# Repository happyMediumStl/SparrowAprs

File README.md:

# SparrowAprs
An open source APRS beacon designed for high altitude balloons

Code is a bit of a mess, and this is a work in progress, but it does sucessfully transmit APRS packets

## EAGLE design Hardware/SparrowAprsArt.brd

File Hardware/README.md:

#SparrowAprs Hardware

Controlled impedance traces designed for 4 layer stackup at Oshpark.

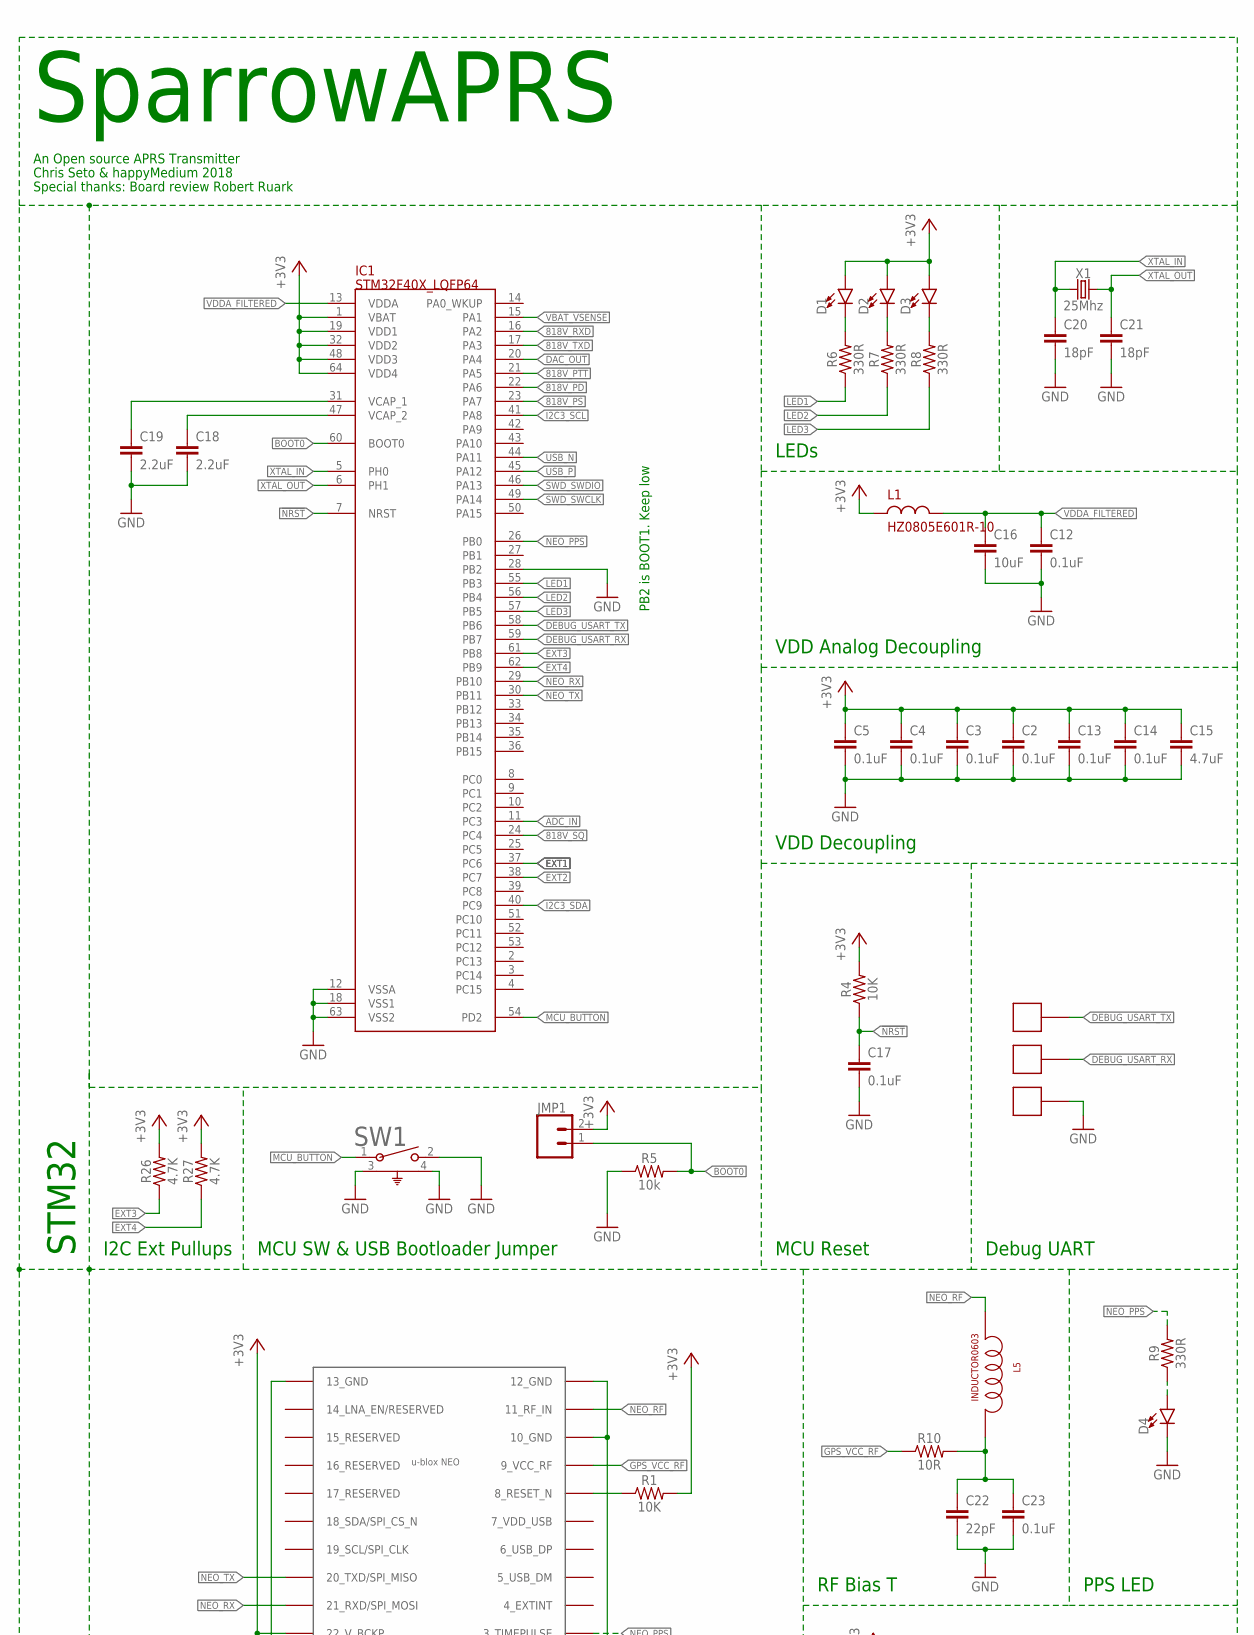
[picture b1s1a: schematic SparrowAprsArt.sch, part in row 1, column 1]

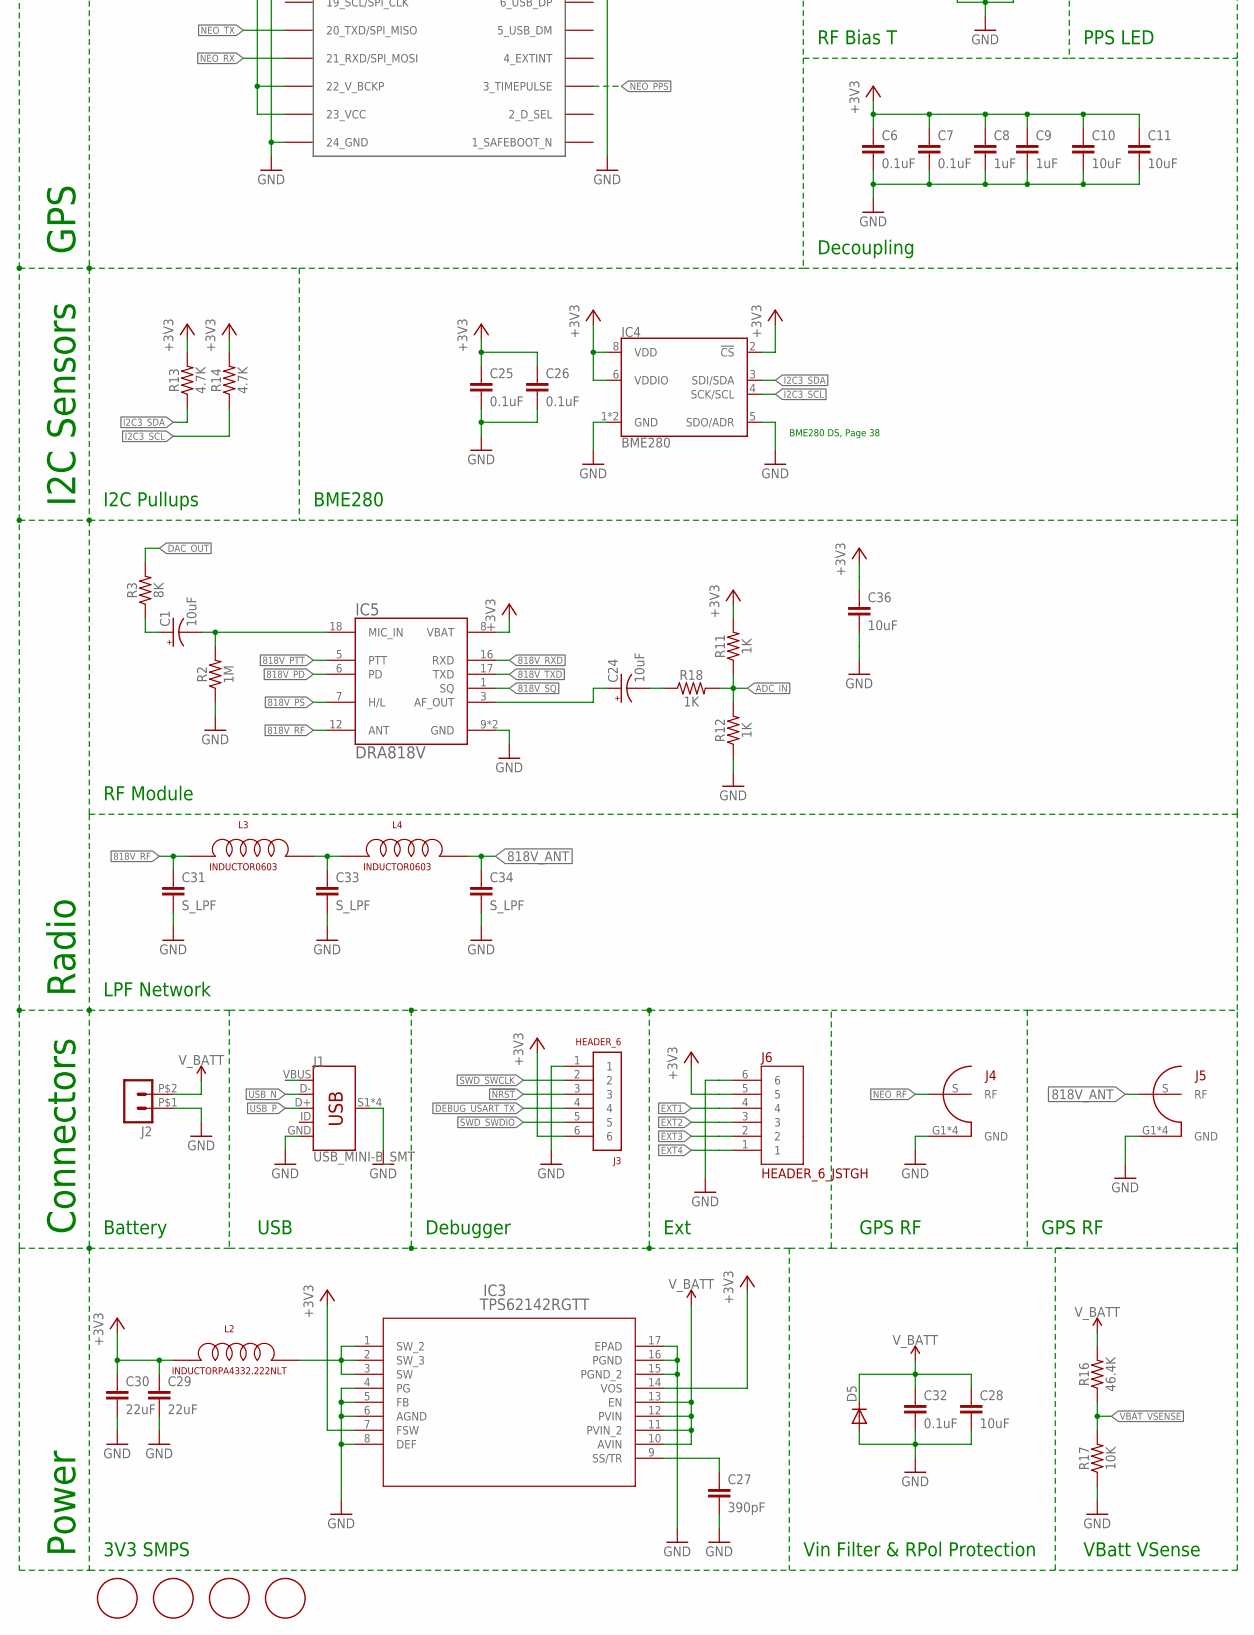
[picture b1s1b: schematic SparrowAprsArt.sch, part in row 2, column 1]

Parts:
C1, C24: 10uF; 1206
C2, C3, C4, C5, C6, C7, C12, C13, C14, C17, C23, C25, C26, C32: 0.1uF; 0603
C8, C9: 1uF; C0805
C10, C11, C16, C28, C36: 10uF; C0805
C15: 4.7uF; C0805
C18, C19: 2.2uF; C0805
C20, C21: 18pF; 0603
C22: 22pF; 0603
C27: 390pF; 0603
C29, C30: 22uF; 1210
C31, C33, C34: S_LPF; 0603
D1, D2, D3, D4: LED0603; LED-0603
D5: DIODE-DO214AC; DO214AC
IC1: STM32F40X_LQFP64; STM32_LQFP64
IC2: NEO-M8
IC3: TPS62142RGTT; RGT16_1P7X1P7
IC4: BME280; LGA-8-2.5X2.5
IC5: DRA818V; DORJI_DRA818V
J1: USB_MINI-B_SMT; USB-MINIB
J2: HEADER_POS2_43650-0200; 43650-0200
J3: HEADER_6; 6X2_SMT
J4, J5: FSK_RUARK2_SMA_0732511150; FSK_RUARK2_WIDE_SMA
J6: HEADER_6_JSTGH; BM06B-GHS-TBT(LF)(SN)(N)
JMP1: CONN_02; 1X02
L1: HZ0805E601R-10; R0805
L2: INDUCTORPA4332.222NLT; PA4332.222NLT
L3, L4, L5: INDUCTOR0603; 0603
R1, R4, R17: 10K; 0603
R2: 1M; 0603
R3: 8K; 0603
R5: 10k; 0603
R6, R7, R8, R9: 330R; 0603
R10: 10R; 0603
R11, R12, R18: 1K; 0603
R13, R14, R26, R27: 4.7K; 0603
R16: 46.4K; 0603
SW1: 1825027-8; SW2_1825027-C
U$2, U$3, U$4: SINGLEPADMIDPAD; MIDPAD
U$7, U$8, U$9, U$10: MOUNTING_HOLE#2; #2_CLEARANCE_HOLE
X1: 25Mhz; CRYSTAL-SMD-3.2X2.5MM

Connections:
818V_ANT: C34.1, J5.S (RF), L4.2
818V_PD: IC1.22 (PA6), IC5.6 (PD)
818V_PS: IC1.23 (PA7), IC5.7 (H/L)
818V_PTT: IC1.21 (PA5), IC5.5 (PTT)
818V_RF: C31.1, IC5.12 (ANT), L3.1
818V_RXD: IC1.16 (PA2), IC5.16 (RXD)
818V_SQ: IC1.24 (PC4), IC5.1 (SQ)
818V_TXD: IC1.17 (PA3), IC5.17 (TXD)
!NRST: C17.1, IC1.7 (NRST), J3.3, R4.1
+3V3: C2.1, C3.1, C4.1, C5.1, C6.1, C7.1, C8.1, C9.1, C10.1, C11.1, C13.1, C14.1, C15.1, C25.1, C26.1, C29.1, C30.1, C36.1, D1.A, D2.A, D3.A, IC1.1 (VBAT), IC1.19 (VDD1), IC1.32 (VDD2), IC1.48 (VDD3), IC1.64 (VDD4), IC2.22 (22_V_BCKP), IC2.23 (23_VCC), IC3.7 (FSW), IC3.14 (VOS), IC4.2 (!CS), IC4.6 (VDDIO), IC4.8 (VDD), IC5.8 (VBAT), J3.6, J6.5, JMP1.2, L1.1, L2.1, R1.2, R4.2, R11.2, R13.2, R14.2, R26.2, R27.2
ADC_IN: IC1.11 (PC3), R11.1, R12.2, R18.2
BOOT0: IC1.60 (BOOT0), JMP1.1, R5.2
DAC_OUT: IC1.20 (PA4), R3.2
DEBUG_USART_RX: IC1.59 (PB7), U$3.1
DEBUG_USART_TX: IC1.58 (PB6), J3.4, U$2.1
EXT1: IC1.37 (PC6), J6.4
EXT2: IC1.38 (PC7), J6.3
EXT3: IC1.61 (PB8), J6.2, R26.1
EXT4: IC1.62 (PB9), J6.1, R27.1
GND: C2.2, C3.2, C4.2, C5.2, C6.2, C7.2, C8.2, C9.2, C10.2, C11.2, C12.2, C13.2, C14.2, C15.2, C16.2, C17.2, C18.2, C19.2, C20.2, C21.2, C22.2, C23.2, C25.2, C26.2, C27.2, C28.2, C29.2, C30.2, C31.2, C32.2, C33.2, C34.2, C36.2, D4.C, D5.A, IC1.12 (VSSA), IC1.18 (VSS1), IC1.28 (PB2), IC1.63 (VSS2), IC2.10 (10_GND), IC2.12 (12_GND), IC2.13 (13_GND), IC2.24 (24_GND), IC3.4 (PG), IC3.5 (FB), IC3.6 (AGND), IC3.8 (DEF), IC3.15 (PGND_2), IC3.16 (PGND), IC3.17 (EPAD), IC4.1 (GND), IC4.5 (SDO/ADR), IC4.7 (GND), IC5.9 (GND), IC5.10 (GND), J1.GND, J1.S1 (SHIELD), J1.S2 (SHIELD), J1.S3 (SHIELD), J1.S4 (SHIELD), J2.P$1 (1), J3.1, J4.G1 (GND), J4.G2 (GND), J4.G3 (GND), J4.G4 (GND), J5.G1 (GND), J5.G2 (GND), J5.G3 (GND), J5.G4 (GND), J6.6, R2.1, R5.1, R12.1, R17.1, SW1.2, SW1.3, SW1.4, U$4.1
GPS_VCC_RF: IC2.9 (9_VCC_RF), R10.1
I2C3_SCL: IC1.41 (PA8), IC4.4 (SCK/SCL), R14.1
I2C3_SDA: IC1.40 (PC9), IC4.3 (SDI/SDA), R13.1
LED1: IC1.55 (PB3), R6.1
LED2: IC1.56 (PB4), R7.1
LED3: IC1.57 (PB5), R8.1
MCU_BUTTON: IC1.54 (PD2), SW1.1
unnamed: C19.1, IC1.31 (VCAP_1)
unnamed: C18.1, IC1.47 (VCAP_2)
unnamed: IC2.8 (8_RESET_N), R1.1
unnamed: D2.C, R7.2
unnamed: D3.C, R8.2
unnamed: D1.C, R6.2
unnamed: C22.1, C23.1, L5.2, R10.2
unnamed: D4.A, R9.1
unnamed: C1.1 (+), R3.1
unnamed: C24.2 (-), R18.1
unnamed: C1.2 (-), IC5.18 (MIC_IN), R2.2
unnamed: C33.1, L3.2, L4.1
unnamed: IC3.1 (SW_2), IC3.2 (SW_3), IC3.3 (SW), L2.2
unnamed: C24.1 (+), IC5.3 (AF_OUT)
unnamed: C27.1, IC3.9 (SS/TR)
NEO_PPS: IC1.26 (PB0), IC2.3 (3_TIMEPULSE), R9.2
NEO_RF: IC2.11 (11_RF_IN), J4.S (RF), L5.1
NEO_RX: IC1.29 (PB10), IC2.21 (21_RXD/SPI_MOSI)
NEO_TX: IC1.30 (PB11), IC2.20 (20_TXD/SPI_MISO)
SWD_SWCLK: IC1.49 (PA14), J3.2
SWD_SWDIO: IC1.46 (PA13), J3.5
USB_N: IC1.44 (PA11), J1.D-
USB_P: IC1.45 (PA12), J1.D+
VBAT_VSENSE: IC1.15 (PA1), R16.1, R17.2
VDDA_FILTERED: C12.1, C16.1, IC1.13 (VDDA), L1.2
V_BATT: C28.1, C32.1, D5.C, IC3.10 (AVIN), IC3.11 (PVIN_2), IC3.12 (PVIN), IC3.13 (EN), J2.P$2 (2), R16.2
XTAL_IN: C20.1, IC1.5 (PH0), X1.1
XTAL_OUT: C21.1, IC1.6 (PH1), X1.3 (2)

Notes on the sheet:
GPS
Radio
I2C Sensors
Battery
Connectors
STM32
Decoupling
RF Bias T
BME280 DS, Page 38
Power
PPS LED
VBatt VSense
I2C Pullups
BME280
VDD Decoupling
MCU Reset
Debug UART
VDD Analog Decoupling
LEDs
Debugger
GPS RF
USB
3V3 SMPS
I2C Ext Pullups
MCU SW & USB Bootloader Jumper
RF Module
LPF Network
Vin Filter & RPol Protection
PB2 is BOOT1. Keep low
Ext
SparrowAPRS
An Open source APRS Transmitter
Chris Seto & happyMedium 2018
Special thanks: Board review Robert Ruark

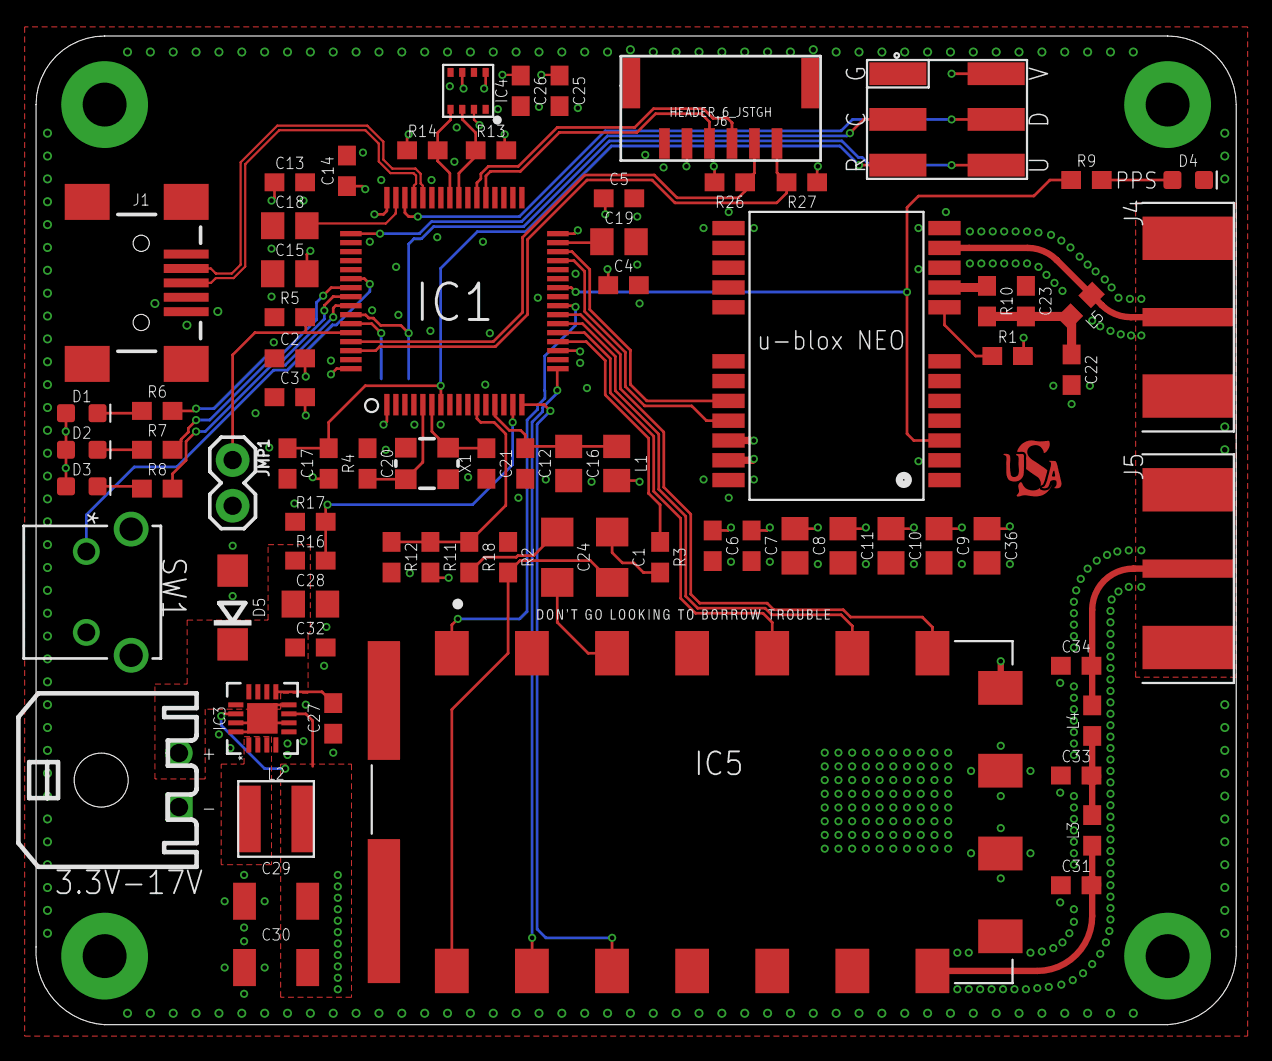
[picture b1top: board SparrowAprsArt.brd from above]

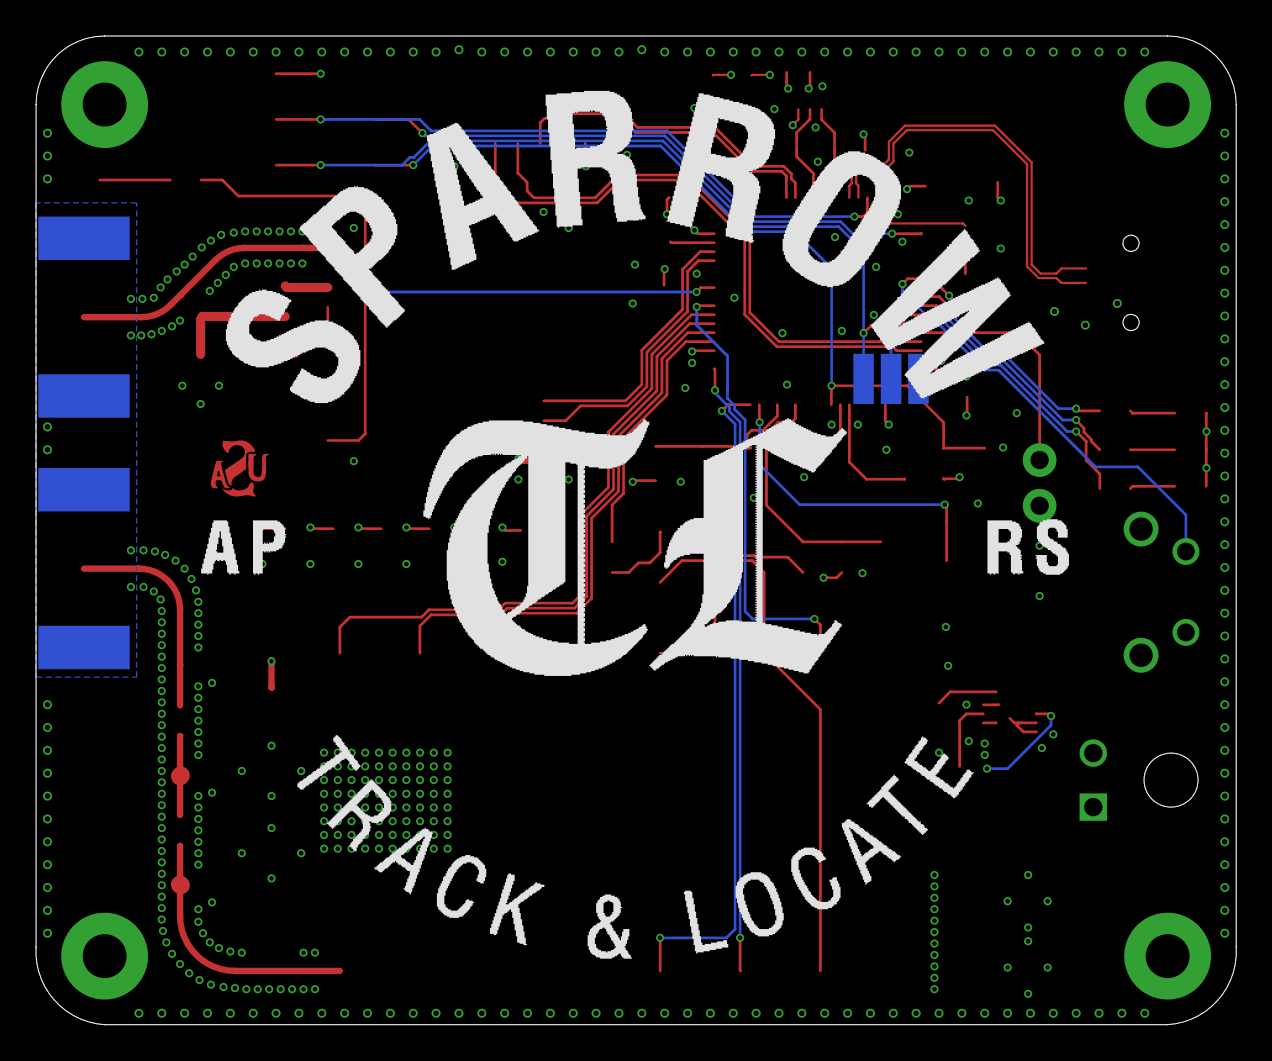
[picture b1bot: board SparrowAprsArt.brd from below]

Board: 4 copper layers, 66.7 x 54.9 mm, 85 parts (3 on the bottom side), 55 nets.

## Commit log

2018-08-13 Added hardware
2018-08-13 Added software
2018-08-13 Added BOM
2018-08-14 Code cleanup, added BSP vSense, fixed filters, added flash config
2018-08-14 More cleanup. BSP now works
2018-08-23 Tested on actual hardware, include BME280 support, include watchdog
2018-08-29 Snapshot. Added USB
2018-08-29 Added vgdb settings
2018-09-07 New hardware rev
2018-09-07 Dev snapshot
2018-09-21 Updated hardware
2018-10-12 Dev snapshot: APRS message tx now works, DRA818V configuration string fix

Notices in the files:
parts and their libraries:
SparkFun-Connectors: Licensing: Creative Commons ShareAlike 4.0 International - https://creativecommons.org/licenses/by-sa/4.0
